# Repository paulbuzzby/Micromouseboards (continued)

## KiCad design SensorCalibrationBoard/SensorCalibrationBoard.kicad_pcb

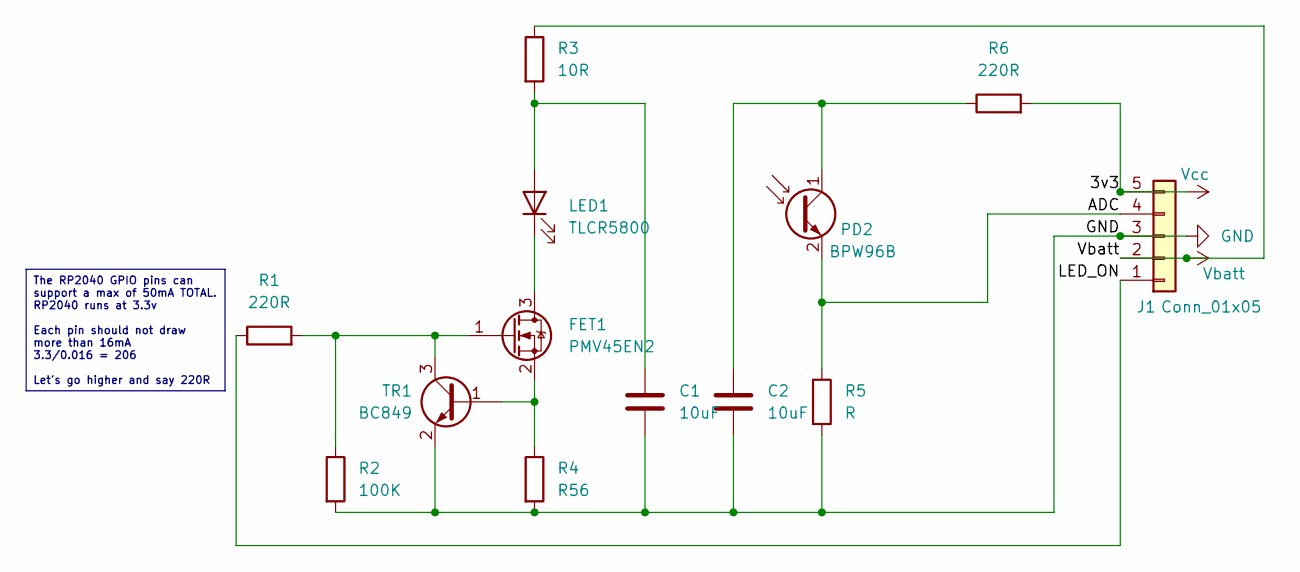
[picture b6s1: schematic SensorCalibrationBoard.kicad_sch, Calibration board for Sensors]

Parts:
C1, C2: 10uF; C_0805_2012Metric
FET1: PMV45EN2; SOT-23_Handsoldering
J1: Conn_01x05; PinHeader_1x05_P2.54mm_Vertical
LED1: TLCR5800; LED_D5.0mm_Horizontal_O1.27mm_Z3.0mm
PD2: BPW96B; LED_D5.0mm_Horizontal_O1.27mm_Z3.0mm
R1, R6: 220R; R_0805_2012Metric
R2: 100K; R_0805_2012Metric
R3: 10R; R_0805_2012Metric
R4: R56; R_0805_2012Metric
R5: R; R_Axial_DIN0207_L6.3mm_D2.5mm_P7.62mm_Horizontal
TR1: BC849; SOT-23_Handsoldering

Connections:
/ADC: J1.4, PD2.2 (E), R5.1
/LED_ON: J1.1, R1.1
GND: C1.2, C2.2, J1.3, R2.2, R4.2, R5.2, TR1.2 (E)
unnamed: FET1.3 (D), LED1.1 (K)
unnamed: FET1.1 (G), R1.2, R2.1, TR1.3 (C)
unnamed: FET1.2 (S), R4.1, TR1.1 (B)
unnamed: C1.1, LED1.2 (A), R3.2
unnamed: C2.1, PD2.1 (C), R6.1
Vbatt: J1.2, R3.1
Vcc: J1.5, R6.2

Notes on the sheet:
The RP2040 GPIO pins can support a max of 50mA TOTAL. RP2040 runs at 3.3v Each pin should not draw more than 16mA 3.3/0.016 = 206 Let's go higher and say 220R

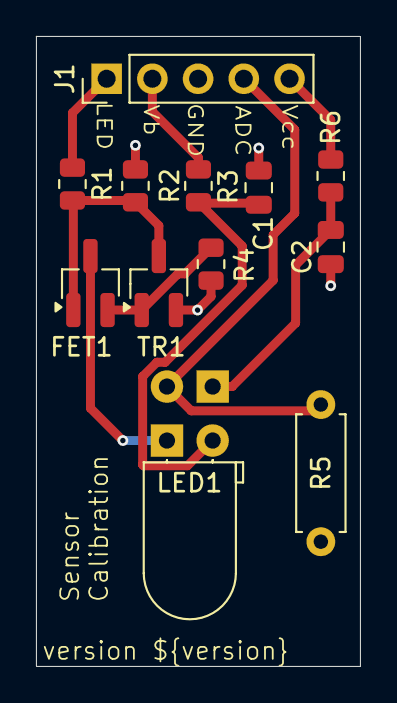
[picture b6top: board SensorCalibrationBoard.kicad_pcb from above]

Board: 2 copper layers, 18.0 x 35.0 mm, 13 parts (1 on the bottom side), 10 nets.

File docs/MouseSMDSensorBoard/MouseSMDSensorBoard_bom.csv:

Reference,Value,Qty,Note,Description
C1 C2,10uF,2,,Unpolarized capacitor
FET1,PMV45EN2,1,,"N-Channel MOSFET, 5.1 A, 30 V, 3-Pin SOT-23"
J1,Conn_01x05,1,,"Generic connector, single row, 01x05, script generated (kicad-library-utils/schlib/autogen/connector/)"
LED1,TLCR5800,1,,Light emitting diode
PD2,BPW96B,1,,Photodiode
PD1,QSB34,1,,Photodiode QSB34 (RS part number 805-0508)
R2,100K,1,,Resistor
R3,10R,1,,Resistor
R1 R6,220R,2,,Resistor
R5,R,1,,Resistor
R4,R56,1,,Resistor
TR1,BC849,1,,"0.1A Ic, 30V Vce, NPN Transistor, SOT-23"

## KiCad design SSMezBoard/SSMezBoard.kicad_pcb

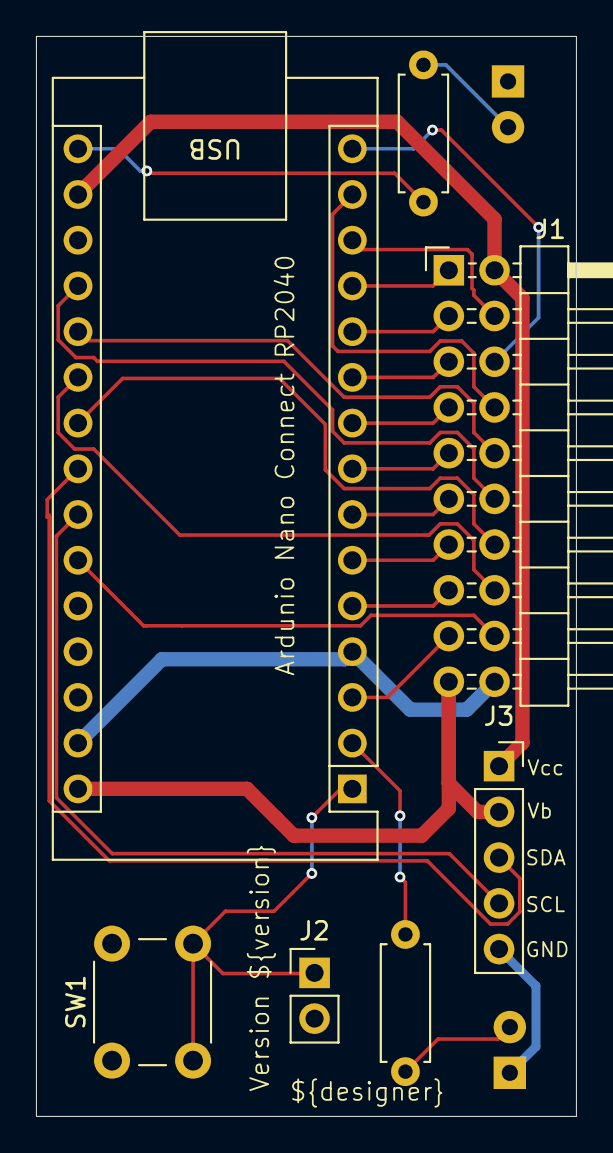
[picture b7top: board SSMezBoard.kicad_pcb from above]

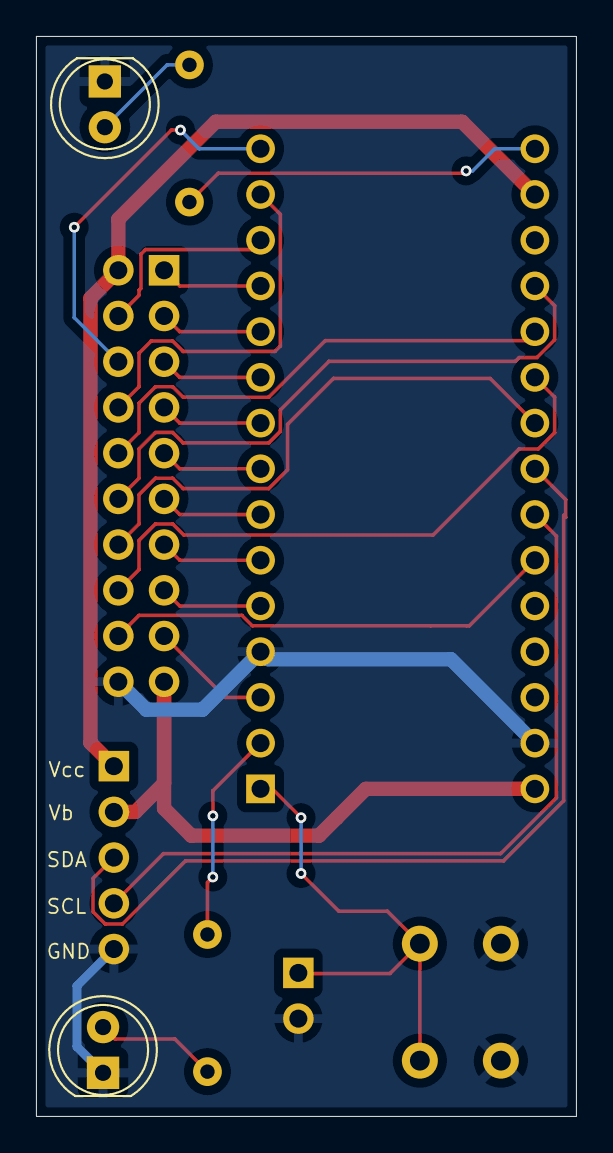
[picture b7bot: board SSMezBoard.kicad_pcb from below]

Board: 2 copper layers, 30.0 x 60.0 mm, 9 parts (2 on the bottom side), 27 nets.

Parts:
A1: Arduino_Nano_RP2040_Connect; Arduino_Nano
D1, D2: LED; LED_D5.0mm
J1: Conn_02x10_Odd_Even; PinHeader_2x10_P2.54mm_Horizontal
J2: Conn_01x02; PinHeader_1x02_P2.54mm_Vertical
J3: Conn_01x05; PinSocket_1x05_P2.54mm_Vertical
R1, R2: 1K; R_Axial_DIN0207_L6.3mm_D2.5mm_P7.62mm_Horizontal
SW1: TACT_SW; SW_PUSH_6mm

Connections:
D18_A6: A1.25 (A6), J1.18
GND: A1.4 (GND), A1.29 (GND), D1.1 (K), D2.1 (K), J1.20, J2.2, J3.5, SW1.1 (A)
GPIO_DIAG: A1.14 (D11/COPI), J1.8
GPIO_FRONT: A1.15 (D12/CIPO), J1.6
LEFT_DIAG_ADC: A1.22 (A3), J1.14
LEFT_ENC_A: A1.11 (D8), J1.3
LEFT_ENC_B: A1.12 (D9), J1.1
LEFT_FRONT_ADC: A1.21 (A2), J1.16
LEFT_Motor_Dir: A1.7 (D4), J1.11
LEFT_Motor_PWM: A1.6 (D3), J1.13
unnamed: A1.2 (D0/RX), R2.1
unnamed: A1.1 (D1/TX), J2.1, SW1.2 (B)
unnamed: A1.16 (D13/SCK), R1.2
unnamed: A1.24 (SCL/A5), J3.4
unnamed: A1.23 (SDA/A4), J3.3
unnamed: D1.2 (A), R2.2
unnamed: D2.2 (A), R1.1
RESET: A1.3 (~RESET), J1.17
RIGHT_DIAG_ADC: A1.19 (A0), J1.12
RIGHT_ENC_A: A1.9 (D6), J1.7
RIGHT_ENC_B: A1.10 (D7), J1.5
RIGHT_FRONT_ADC: A1.20 (A1), J1.10
RIGHT_Motor_Dir: A1.8 (D5), J1.9
RIGHT_Motor_PWM: A1.5 (D2), J1.15
SENSOR_LED: A1.13 (D10/CS), J1.4
Vbatt: A1.30 (VIN), J1.19, J3.2
Vcc: A1.17 (3V3), J1.2, J3.1

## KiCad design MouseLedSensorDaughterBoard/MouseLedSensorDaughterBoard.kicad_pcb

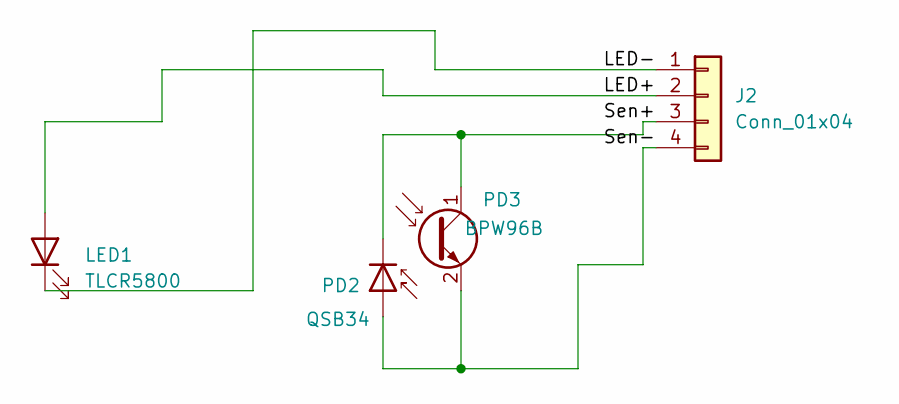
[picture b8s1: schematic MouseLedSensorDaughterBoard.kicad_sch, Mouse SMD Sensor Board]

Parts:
J2: Conn_01x04; PinHeader_1x04_P2.54mm_Vertical
LED1: TLCR5800; LED_D5.0mm
PD2: QSB34; PLCC_2L_Handsoldering
PD3: BPW96B; LED_D5.0mm_Clear

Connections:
/LED+: J2.2, LED1.2 (A)
/LED-: J2.1, LED1.1 (K)
/Sen+: J2.3, PD2.1 (K), PD3.1 (C)
/Sen-: J2.4, PD2.2 (A), PD3.2 (E)

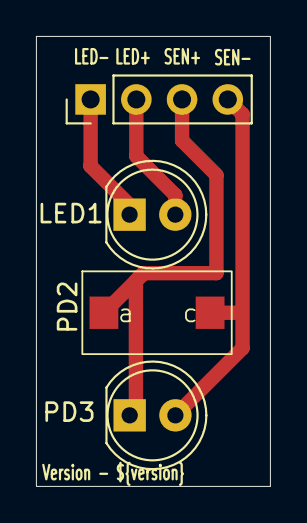
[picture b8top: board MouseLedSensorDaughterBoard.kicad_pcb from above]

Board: 2 copper layers, 13.0 x 25.0 mm, 4 parts (0 on the bottom side), 4 nets.

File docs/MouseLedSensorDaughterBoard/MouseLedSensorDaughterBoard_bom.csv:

Reference,Value,Qty,Note,Description
J2,Conn_01x04,1,,"Generic connector, single row, 01x04, script generated (kicad-library-utils/schlib/autogen/connector/)"
LED1,TLCR5800,1,,Light emitting diode
PD3,BPW96B,1,,Phototransistor NPN
PD2,QSB34,1,,Photodiode VEMD4010X01

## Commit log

2025-01-25 Boards init checkin
2025-01-26 PDF exports
2025-01-29 Updates based on feedback
2025-02-02 Sort of ready for JLCPCB
2025-04-15 Version 2 of boards sent to JLCPCB and a new calibration board
2025-08-15 Checkin to baseline everything
2025-08-15 KiCad Automation
2025-08-15 docs: update KiCad exports [skip ci]
2025-08-19 Send boards to JLCPCB
2025-12-11 updates before complete rearrange
2026-01-22 before updating to KiCad 9 and changing sensor design
2026-01-29 first draft of new board all layout complete
2026-01-30 update workflow to use kicad 9
2026-01-31 First version of v4 board ready for production
2026-02-03 updated sensor locations, all resistors are back to be 0805, routing changes and moved the motor controller around plus other changes from Peter's suggestions
2026-02-03 routing changes
2026-02-03 Not sure what happened
2026-02-04 trace tweaks
2026-02-08 New board sent to JLCPCB for new Chassis
